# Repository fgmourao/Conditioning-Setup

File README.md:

# Conditioning Setup v2.0
** Under development

Hardware, firmware and desktop interface for classical fear conditioning.
Arduino DUE stimulus generator controlled by a Python/PyQt5 application over USB.

---

## Origin

This project is a full rewrite of the system described in:

> Amaral Junior PA, Mourao FAG, Moraes MFD (2019).
> *A Custom Microcontrolled and Wireless-Operated Chamber for Auditory Fear Conditioning.*
> Frontiers in Neuroscience.
> https://doi.org/10.3389/fnins.2019.01193

The original v1.0 architecture used an ESP8266 as a Wi-Fi master communicating with the Arduino DUE via SPI, with a browser-based HTML interface. Version 2.0 removes the ESP8266 entirely — a PyQt5 desktop application communicates directly with the DUE over its native USB port.

Beyond the architectural change, v2.0 introduces several new capabilities: adaptive DAC lookup tables for lower harmonic distortion across the full frequency range, an AM modulation channel with configurable modulator frequency, two independent programmable digital trigger outputs (pins 10 and 11) for synchronising external equipment, an OLED status display, a hardware watchdog with fault detection, and a calibration interface with per-bar shock selection.

---

## Changes from v1.0 to v2.0

### Architecture
The ESP8266 Wi-Fi master and SPI bus are removed entirely. Python communicates directly with the DUE over its native USB port using newline-terminated JSON. All stimulus timing is handled autonomously by the DUE after a single `start` command — no real-time control from the host is required during execution.

### Bug fixes and stability improvements

**Shock clock decoupled from DAC** — in v1.0 the shock interval counter (`iCountShockIntervals`) was incremented inside the `carrier()` ISR, which ran at the DAC rate. Changing `carrier_freq` silently altered shock pulse timing. In v2.0 the shock has its own dedicated Timer6 running at a fixed 10 kHz, completely independent of the DAC.

**Hardware ABORT pin pullup** — in v1.0 `pinABORT` was configured as `INPUT` with no pullup resistor, leaving the pin floating when the button was not pressed and susceptible to spurious aborts from electrical noise. In v2.0 it uses `INPUT_PULLUP`.

**DAC disabled between sounds** — in v1.0 `analogWrite(DAC1, 0)` at sound offset wrote zero but left the DAC channel enabled, injecting DC noise into the amplifier between trials. In v2.0 `dacc_disable_channel` is called at every sound offset and the coupling capacitor is pre-charged to midscale before each onset to eliminate transients.

**Shock pulse timing precision** — in v1.0 `floor()` was used to convert pulse times to tick counts, introducing a systematic downward truncation error. In v2.0 `roundf()` gives the nearest tick (0.1 ms resolution at 10 kHz).

**Watchdog** — v1.0 had no hardware fault detection. If Timer4 or Timer6 stalled, the experiment continued silently with no stimuli. In v2.0 a software watchdog monitors both timers; if either stops incrementing for 5 seconds a fault is declared, all outputs are driven LOW, and the Python interface displays a critical alert.

**DAC buffer type** — in v1.0 the DAC buffer was `uint32_t` (4 bytes per sample), wasting twice the RAM needed. In v2.0 it is `uint16_t` (2 bytes per sample), halving the buffer footprint to 2 KB.

### Sound generation

In v1.0 the carrier lookup table had a fixed 8 samples regardless of frequency. At low carrier frequencies (1–3 kHz) this produced visible harmonic distortion — only 8 points approximated each sine cycle. In v2.0 adaptive tables select 4, 8, 16, or 32 samples based on the carrier frequency, keeping the DAC update rate within the optimal range across the full 0–20 kHz span.

### New stimuli and features

- **LIGHT** — independent light stimulus (pin 45, square wave or DC HIGH) with its own onset, duration, and frequency per trial
- **Trigger 1 / Trigger 2** — two independent digital pulse outputs (pins 10 and 11) for synchronising external equipment, with configurable onset (s) and duration (ms) per trial
- **Baseline period** — quiet time before the first trial, separate from the inter-trial interval
- **Per-trial volume control** — sound amplitude programmable per trial (0–100%)
- **AM modulation** — configurable modulator frequency per trial; `modulator_freq = 0` gives a pure sine
- **OLED status display** — real-time trial state on an SSD1306 128×32 display
- **Bar selection** — calibration mode allows fixing a single shock bar for individual verification
- **Python desktop interface** — replaces the ESP8266 HTML page with a PyQt5 application featuring a trial timeline preview, protocol save/load, event log, and calibration dialogs

---

## Architecture

```
Python / PyQt5  (PC)
      │
      │  SerialUSB — native USB port (USB CDC)
      │
Arduino DUE
      ├─ DAC1         →  Sound  (AM sine, 0–20 kHz)
      ├─ Timer4/5     →  DAC clock / AM modulator ISR
      ├─ Timer6       →  Shock clock (10 kHz)
      ├─ Timer7       →  Light square wave
      ├─ Pins 23–37   →  Shock bars (8 outputs, random sequence per trial)
      ├─ Pin 45       →  Light output
      ├─ Pin 46       →  Watchdog fault output
      ├─ Pin 48       →  Hardware ABORT input
      ├─ Pin 10        →  Trigger 1 output (digital pulse)
      ├─ Pin 11        →  Trigger 2 output (digital pulse)
      ├─ Pins 50–53   →  Sync outputs (SOUND, LIGHT, SHOCK, MOD)
      └─ Pins 20–21   →  I²C — OLED display (SDA / SCL)
```

The DUE stores the complete trial list in RAM and executes the experiment autonomously after a single `start` command. Python is responsible only for programming parameters, triggering execution, and monitoring status.

---

## Stimuli

Five independent stimuli with individual onset and duration per trial:

### Sound
- Output: DAC1 (12-bit, 0–3.3 V)
- Waveform: AM-modulated sine (`SINE_AM`) or pure sine
- Carrier: 0–20 kHz; modulator: 0–500 Hz
- Adaptive lookup tables (see [Sound generation](#sound-generation))
- AC coupling capacitor (10 µF) recommended in series on DAC1 output

### Light
- Output: pin 45, square wave 50% duty cycle
- Frequency: configurable; `light_freq = 9999` = DC HIGH (constant ON)

### Shock
- Outputs: pins 23, 25, 27, 29, 31, 33, 35, 37 (8 bars)
- Random sequence (Fisher-Yates shuffle) activation or fixed single bar (calibration)
- Pulse HIGH and LOW times configurable in ms (0.1 ms resolution at 10 kHz clock)

### Trigger 1 / Trigger 2
- Outputs: pin 10 (Trigger 1), pin 11 (Trigger 2)
- Simple digital HIGH pulse: onset in seconds, duration in milliseconds
- Independent of each other and of all other stimuli
- Intended for synchronising external equipment (cameras, stimulators, recording systems)

---

## Trial structure

Each trial stores 20 float parameters, transmitted semicolon-separated over serial:

| Field | Description | Unit |
|---|---|---|
| `baseline` | Quiet period before first trial | s |
| `silence` | Inter-trial interval | s |
| `onset_sound` | Sound onset within trial | s |
| `sound_duration` | Sound duration | s |
| `carrier_freq` | DAC carrier frequency; 0 = no sound | Hz |
| `modulator_freq` | AM modulator frequency; 0 = pure sine | Hz |
| `volume` | Sound amplitude | % |
| `waveform_type` | 0 = SINE_AM, 1 = SINE, 2 = SQUARE | — |
| `onset_shock` | Shock onset within trial | s |
| `shock_duration` | Shock duration; 0 = no shock | s |
| `pulse_high` | Shock bar ON time per pulse | ms |
| `pulse_low` | Shock bar OFF time between pulses | ms |
| `onset_light` | Light onset within trial | s |
| `light_duration` | Light duration; 0 = no light | s |
| `light_freq` | Light frequency; 9999 = DC HIGH | Hz |
| `bar_select` | 0 = Random sequence per trial, 1–8 = fixed bar, , 9 = sequential 1→8 (calibration "All") | — |
| `onset_trig1` | Trigger 1 onset within trial; 0 = start of trial | s |
| `trig1_duration` | Trigger 1 pulse duration; 0 = disabled | ms |
| `onset_trig2` | Trigger 2 onset within trial; 0 = start of trial | s |
| `trig2_duration` | Trigger 2 pulse duration; 0 = disabled | ms |

---

## Serial protocol

All communication uses newline-terminated JSON objects:

```
{"cmd":"ping"}
    -> {"ok":true,"msg":"pong","version":"2.0"}

{"cmd":"program","n":N,"data":"f0;f1;..."}
    -> {"ok":true,"msg":"N trials programmed"}

{"cmd":"start"}
    -> {"ok":true,"msg":"started"}

{"cmd":"abort"}
    -> {"ok":true,"msg":"aborted"}

{"cmd":"status"}
    -> {"ok":true,"status":N,"trial":N,"total":N,
        "running":bool,"ready":bool,"fault":bool}
```

Status codes: `0` IDLE · `1` READY · `2` RUNNING · `3` DONE · `4` FAULT · `5` ABORTED

---

## Sync outputs

All sync pins are active HIGH while the corresponding stimulus is active.
**Use these pins as the authoritative timing reference for external equipment** (electrophysiology, cameras). The `onset_*` fields in seconds carry a worst-case jitter of ~500 µs (one loop iteration); the sync pins do not.

| Pin | Signal | Description |
|---|---|---|
| 50 | SOUND_SYN | HIGH while sound is playing |
| 51 | LIGHT_SYN | HIGH while light is active |
| 52 | SHOCK_SYN | HIGH while shock is being delivered |
| 53 | MOD_SYN | Square wave at `modulator_freq`, phase-locked to AM envelope |

---

## OLED status display

Optional SSD1306 128×32 OLED on I²C (SDA = pin 20, SCL = pin 21, address 0x3C).
Shows experiment state at each transition:

| State | Display |
|---|---|
| Startup | `Conditioning Setup / Version 2.0` |
| Trial onset | `TRIAL X/N` / `CS` · `CS + US` · `US` |
| Done | `Conditioning Setup / Done` |
| Aborted | `Conditioning Setup / Aborted` |

The firmware runs normally if the display is not connected.

---

## Sound generation

v2.0 uses adaptive lookup tables (`Waveforms.h`) to minimise harmonic distortion across the full frequency range:

| Carrier frequency | Table size | DAC update rate |
|---|---|---|
| > 10 000 Hz | 4 samples | up to 80 kHz |
| > 3 000 Hz | 8 samples | up to 80 kHz |
| > 1 000 Hz | 16 samples | up to 48 kHz |
| ≤ 1 000 Hz | 32 samples | up to 32 kHz |

All rates are within the SAM3X8E DAC hardware limit of 1 MHz.
Buffer RAM cost: 32 × 32 × 2 bytes = 2 KB.

AM modulation uses a 32-sample unipolar envelope table. When `modulator_freq = 0` the carrier is output as a pure sine with no modulation.

---

## DAC signal conditioning

The DAC1 output is 0–3.3 V (unipolar, midscale = 1.65 V DC). A signal conditioning chain is required before the amplifier or speaker.

### Signal chain

```
DAC1 ── 10 µF (AC coupling) ── [ON-OFF-ON switch] ─┬─ Path A: direct output (external amplifier / measurement)
                                                  └─ Path B: Rs (12 kΩ) ── Rp (1 kΩ to GND)
                                                                     │
                                                                  POT (50 kΩ linear)
                                                                     │ cursor
                                                                  TDA8932 IN+
                                                                     │
                                                               OUT1 ── tweeter ── OUT2
```

### Components

| Component | Value | Purpose |
|---|---|---|
| C1 electrolytic | 10 µF, + toward DAC1 | Blocks 1.65 V DC offset; passes AC signal |
| Rs fixed resistor | 12 kΩ | Attenuates DAC signal to prevent amplifier saturation |
| Rp fixed resistor | 1 kΩ to GND | Anchors amplifier input when DAC is disabled; eliminates idle noise |
| Potentiometer | 50 kΩ linear | Volume control across full rotation range without clipping |
| TDA8932 module | Class-D, 12 V, BTL | Gain 30 dB (31.6×); differential output OUT1/OUT2 |
| Tweeter | 4 Ω, 40 W, 6–20 kHz | Connected differentially between OUT1 and OUT2 |

### ON-OFF-ON switch

A three-position toggle switch after the coupling capacitor selects the signal path:

| Position | Path | Use |
|---|---|---|
| ON (left) | Direct output after C1 | External amplifier, oscilloscope, audio interface |
| OFF (centre) | Mute | No signal at any output |
| ON (right) | Rs → Rp → POT → TDA8932 → tweeter | Normal experimental operation |

---

## Python application

### Requirements

```
pip install pyserial PyQt5
```

Python 3.8 or later.

### Features

- Dark/Light-theme PyQt5 desktop application
- Trial configuration panel: per-stimulus onset, duration, frequency, volume, pulse timing, trigger durations
- Recorded trials table with per-row delete
- Timeline preview: block diagram of all trials on a shared time axis with a real-time progress line during execution; rows are shown only for stimuli with non-zero duration
- Event log with timestamps (`YYYY-MM-DD HH:MM:SS`) — exportable via Save Log
- **Protocol menu:** Save Protocol, Load Protocol, Clear All Trials, Save Log
- **Calibration menu:** Sound, Light, Shock — continuous single-trial stimulus stopped by ABORT; shock calibration allows bar selection and configurable pulse timing
- **Help menu:** Info dialog
- Port selector with refresh button
- 4-second timeout warning if DUE does not respond after connection
- Firmware version check on connect (warns if not v2.0)
- Watchdog fault popup with critical alert
- Hardware ABORT button (pin 48) is read inside the trial timing loop and during inter-trial silences — responsive at any point during experiment execution

### Poll strategy

The poll timer (`{"cmd":"status"}` every 1500 ms) is stopped when the experiment starts to prevent USB interrupt collisions with Timer4 on the Native Port. One poll is scheduled at the calculated onset of each trial using `QTimer.singleShot`. A generation counter invalidates scheduled polls that remain pending after an ABORT. The poll timer resumes when the experiment ends or is aborted.

---

## Hardware requirements

| Component | Specification |
|---|---|
| Microcontroller | Arduino DUE |
| USB connection | Native port (second USB connector) |
| Shock bars | 8 outputs — pins 23, 25, 27, 29, 31, 33, 35, 37 |
| Light output | Pin 45 |
| Trigger 1 output | Pin 10 — digital pulse |
| Trigger 2 output | Pin 11 — digital pulse |
| ABORT button | Momentary switch — pin 48 to GND |
| DAC coupling | 10 µF electrolytic capacitor in series on DAC1 |
| Amplifier | Class-D module (e.g. TDA8932); 10–50 kΩ potentiometer at input |
| Speaker | Tweeter (2–20 kHz); 4 Ω or 8 Ω |
| OLED (optional) | SSD1306 128×32, I²C, address 0x3C |

---

## Files

| File | Description |
|---|---|
| `conditioning_setup_dark.py` | Main application — dark theme |
| `Stimuli_PY_DUE.ino` | Arduino DUE firmware |
| `Waveforms.h` | Adaptive DAC lookup tables |
| `image.png` | Logo displayed in the application header |

Arduino library dependencies (install via Arduino IDE Library Manager):
- **DueTimer** (Ivan Seidel)
- **Adafruit GFX Library**
- **Adafruit SSD1306**

---

## Desktop Executables

Pre-built executables are available for macOS and Windows. No Python installation is required — all dependencies are bundled inside the application package.

### macOS

**File:** `Conditioning Setup.app`

**Compatibility:** Built on Apple Silicon (M-series); runs natively on Apple Silicon Macs only.

**Installation:**
1. Download `Conditioning Setup.app`
2. Move it to your Applications folder or any preferred location
3. On first launch, macOS Gatekeeper may block the app because it is not signed by an Apple-registered developer. To allow it, open Terminal and run:

```bash
xattr -cr "/Applications/Conditioning Setup.app"
```

Then double-click the app to open normally.

**Build environment:**
- macOS 15.7.5 (Sequoia), Apple Silicon (M2)
- Python 3.12.2
- PyInstaller 6.x
- PyQt5 5.15.x, pyserial 3.x

**Build command:**
```bash
pyinstaller --windowed \
    --name "Conditioning Setup" \
    --icon "icon.icns" \
    --add-data "image.png:." \
    conditioning_setup_dark.py
```

---

### Windows

**File:** `Conditioning Setup.exe`

**Compatibility:** Windows 10 and Windows 11 (64-bit). Built on Windows 11; compatible with Windows 10 version 1903 or later.

**Installation:**
1. Download `Conditioning Setup.exe`
2. Place it in any folder
3. On first launch, Windows SmartScreen may display a warning ("Windows protected your PC"). Click **More info** → **Run anyway**. This warning appears because the executable is not digitally signed.

**USB driver:** the Arduino DUE native port uses a standard USB CDC driver. Windows 10 and 11 include this driver natively — no additional installation is required in most cases. If the COM port is not recognised, install the SAM-BA driver from the Arduino IDE or from the Microchip website.

**Build environment:**
- Windows 11, 64-bit
- Python 3.14.5
- PyInstaller 6.20.0
- PyQt5 5.15.x, pyserial 3.x

**Build command:**
```
py -m PyInstaller --onefile --windowed --name "Conditioning Setup" --icon "icon.ico" --add-data "image.png;." --add-data "icon.ico;." conditioning_setup_dark.py
```

---

## Known limitations

- Noise waveforms (white, pink) are not implemented. The lookup-table architecture is periodic; a possible approach is to generate noise buffers in Python (NumPy/SciPy) and send them as custom tables over serial.
- If the USB cable is disconnected during an experiment, the DUE continues executing autonomously. The only way to stop it is the hardware ABORT button (pin 48).

---

## License

Documentation licensed under Creative Commons Attribution-NonCommercial 4.0 International (CC BY-NC 4.0).

---

## Authors

**v1.0 (2019)**
Paulo Aparecido Amaral Junior, Flavio Afonso Goncalves Mourao, Marcio Flavio Dutra Moraes
*Núcleo de Neurociências, Federal University of Minas Gerais, Brazil*

**v2.0 (2026)**
Flavio Afonso Goncalves Mourao — [mourao.fg@gmail.com](mailto:mourao.fg@gmail.com)
*CNPq/MCTI/FNDCT Nº 21/2024 — Processo 446467/2024-3*
*Federal University of Minas Gerais, Brazil*

---

*Last update: June 2026*

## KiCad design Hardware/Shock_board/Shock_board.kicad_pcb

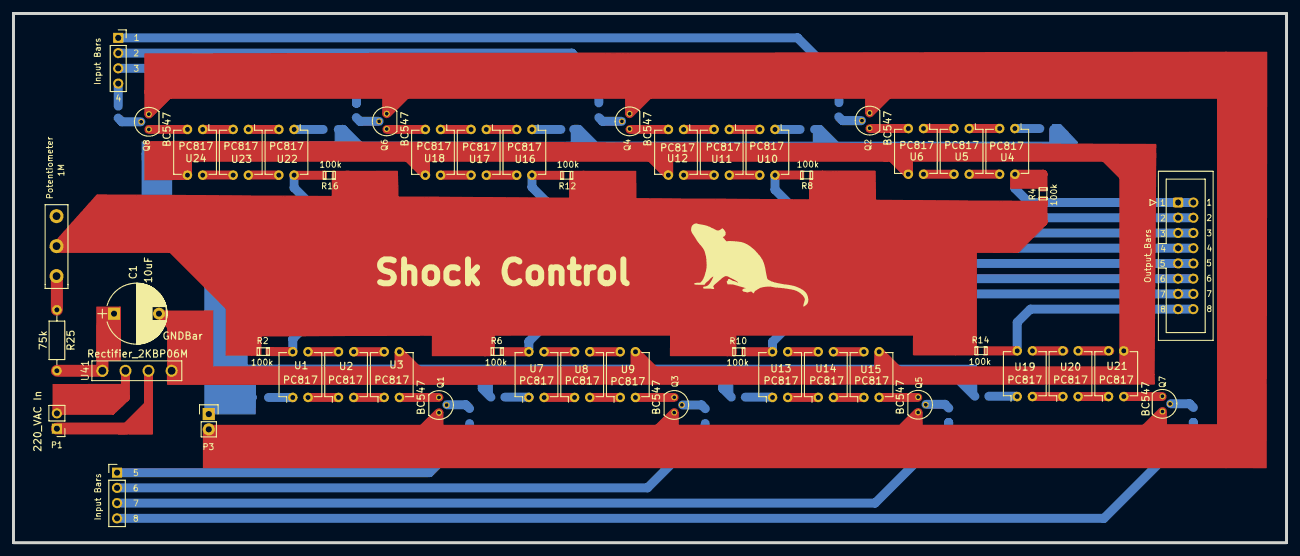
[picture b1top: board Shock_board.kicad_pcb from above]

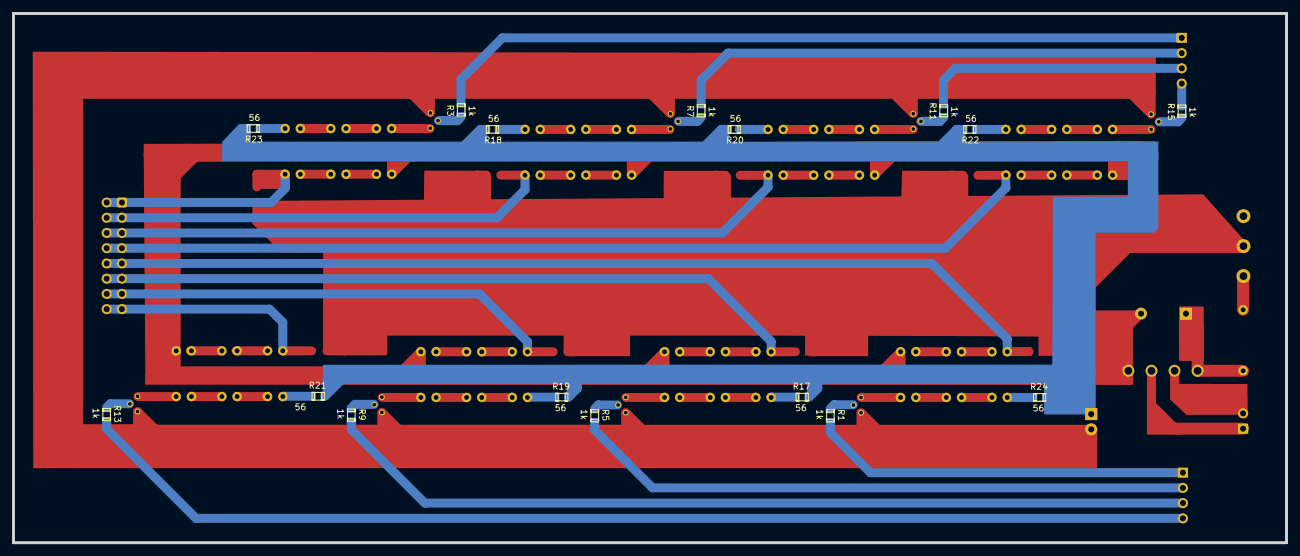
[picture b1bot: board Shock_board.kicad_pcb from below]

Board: 2 copper layers, 212.3 x 88.3 mm, 65 parts (16 on the bottom side), 80 nets.

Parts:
C1: 10uF; CP_Radial_D10.0mm_P7.50mm
Input Bars: PinHeader_1x04_P2.54mm_Vertical
Input Bars#2: PinSocket_1x04_P2.54mm_Vertical
Output_Bars: IDC-Header_2x08_P2.54mm_Vertical
P1: 220_VAC In; Pin_Header_Straight_1x02_Pitch2.54mm
P3: 5_VDC In; Pin_Header_Straight_1x02
Potentiometer: 1M; Potentiometer_Alps_RK163_Single_Vertical
Q1, Q2, Q3, Q4, Q5, Q6, Q7, Q8: BC547; TO-92_Molded_Narrow
R1, R3, R5, R7, R9, R11, R13, R15: 1k; SMD_0805
R2, R4, R6, R8, R10, R12, R14, R16: 100k; SMD_0805
R17, R18, R19, R20, R21, R22, R23, R24: 56; SMD_0805
R25: 75k; R_Axial_DIN0207_L6.3mm_D2.5mm_P10.16mm_Horizontal
U1, U2, U3, U4, U5, U6, U7, U8, U9, U10, U11, U12, U13, U14, U15, U16, U17, U18, U19, U20, U21, U22, U23, U24: PC817; DIP-4_W7.62mm
U41: Rectifier_2KBP06M

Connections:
5V_Arduino: P3.1, R17.2, R18.2, R19.2, R20.2, R21.2, R22.2, R23.2, R24.2
/InBarra1: Input Bars.1, R1.2
/InBarra2: Input Bars#2.1, R3.2
/InBarra3: Input Bars.2, R5.2
/InBarra4: Input Bars#2.2, R7.2
/InBarra5: Input Bars.3, R9.2
/InBarra6: Input Bars#2.3, R11.2
/InBarra7: Input Bars.4, R13.2
/InBarra8: Input Bars#2.4, R15.2
/OutBarra1: Output_Bars.9, Output_Bars.10, R2.2, U1.4
/OutBarra2: Output_Bars.1, Output_Bars.2, R4.2, U4.4
/OutBarra3: Output_Bars.11, Output_Bars.12, R6.2, U7.4
/OutBarra4: Output_Bars.3, Output_Bars.4, R8.2, U10.4
/OutBarra5: Output_Bars.13, Output_Bars.14, R10.2, U13.4
/OutBarra6: Output_Bars.5, Output_Bars.6, R12.2, U16.4
/OutBarra7: Output_Bars.15, Output_Bars.16, R14.2, U19.4
/OutBarra8: Output_Bars.7, Output_Bars.8, R16.2, U22.4
/Vtrafo+: P1.1, U41.3
/Vtrafo-: P1.2, U41.2
GndArduino: P3.2, Q1.3 (E), Q2.3 (E), Q3.3 (E), Q4.3 (E), Q5.3 (E), Q6.3 (E), Q7.3 (E), Q8.3 (E)
GndBarra: C1.2, U3.3, U6.3, U9.3, U12.3, U15.3, U18.3, U21.3, U24.3, U41.4 (-)
unnamed: Q1.2 (B), R1.1
unnamed: Q1.1 (C), U3.2
unnamed: Q2.2 (B), R3.1
unnamed: Q2.1 (C), U6.2
unnamed: Q3.2 (B), R5.1
unnamed: Q3.1 (C), U9.2
unnamed: Q4.2 (B), R7.1
unnamed: Q4.1 (C), U12.2
unnamed: Q5.2 (B), R9.1
unnamed: Q5.1 (C), U15.2
unnamed: Q6.2 (B), R11.1
unnamed: Q6.1 (C), U18.2
unnamed: Q7.2 (B), R13.1
unnamed: Q7.1 (C), U21.2
unnamed: Q8.2 (B), R15.1
unnamed: Q8.1 (C), U24.2
unnamed: R17.1, U7.1
unnamed: R18.1, U10.1
unnamed: R19.1, U13.1
unnamed: R20.1, U16.1
unnamed: R21.1, U19.1
unnamed: R22.1, U22.1
unnamed: R23.1, U4.1
unnamed: R24.1, U1.1
unnamed: Potentiometer.3, R25.1
unnamed: U1.2, U2.1
unnamed: U1.3, U2.4
unnamed: U2.2, U3.1
unnamed: U2.3, U3.4
unnamed: U4.2, U5.1
unnamed: U4.3, U5.4
unnamed: U5.2, U6.1
unnamed: U5.3, U6.4
unnamed: U7.2, U8.1
unnamed: U7.3, U8.4
unnamed: U8.2, U9.1
unnamed: U8.3, U9.4
unnamed: U10.2, U11.1
unnamed: U10.3, U11.4
unnamed: U11.2, U12.1
unnamed: U11.3, U12.4
unnamed: U13.2, U14.1
unnamed: U13.3, U14.4
unnamed: U14.2, U15.1
unnamed: U14.3, U15.4
unnamed: U16.2, U17.1
unnamed: U16.3, U17.4
unnamed: U17.2, U18.1
unnamed: U17.3, U18.4
unnamed: U19.2, U20.1
unnamed: U19.3, U20.4
unnamed: U20.2, U21.1
unnamed: U20.3, U21.4
unnamed: U22.2, U23.1
unnamed: U22.3, U23.4
unnamed: U23.2, U24.1
unnamed: U23.3, U24.4
unnamed: C1.1, R25.2, U41.1 (+)
Vbarra: Potentiometer.2, R2.1, R4.1, R6.1, R8.1, R10.1, R12.1, R14.1, R16.1

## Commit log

2026-05-20 update_May_20_2026
2026-05-26 update May 26,2026
2026-05-31 update_Sat May,30 2026
2026-05-31 Update_Sat_May_30_2026
2026-05-31 update_images
2026-06-02 Update_Jun 02 2026
2026-06-26 Update - Jun 26, 2026
